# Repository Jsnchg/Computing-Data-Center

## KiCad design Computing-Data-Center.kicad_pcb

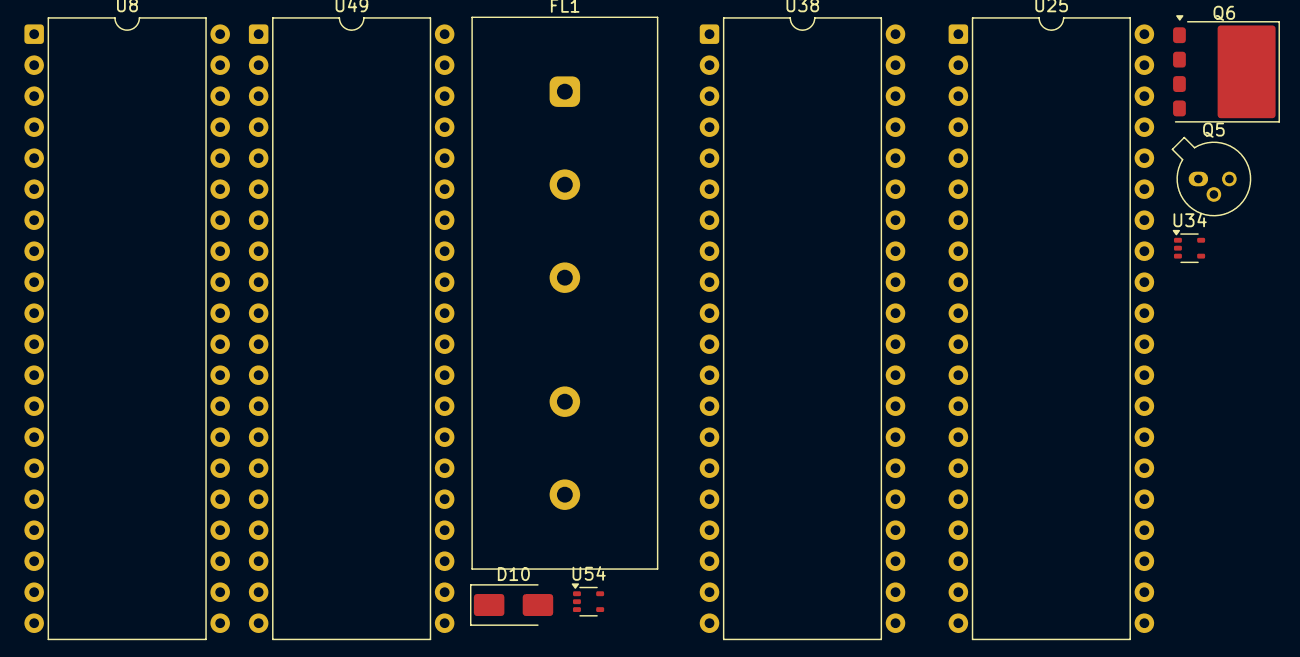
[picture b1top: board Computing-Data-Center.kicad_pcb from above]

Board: 2 copper layers, 10 parts (0 on the bottom side), 2 nets, no tracks yet.

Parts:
D10: NRVA4005T3G; D_SMA
FL1: FN406-0.5-02; Filter_Schaffner_FN406
Q5: BC107; TO-18-3
Q6: SCTL35N65G2V; ST_PowerFLAT_HV-5_8x8mm
U8, U25, U38, U49: 8080; DIP-40_W15.24mm
U34, U54: TLV172IDCK; SOT-353_SC-70-5

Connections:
unnamed: Q5.1 (E), Q5.2 (B), Q5.3 (C)
unnamed: Q6.3 (S), Q6.4 (S)
